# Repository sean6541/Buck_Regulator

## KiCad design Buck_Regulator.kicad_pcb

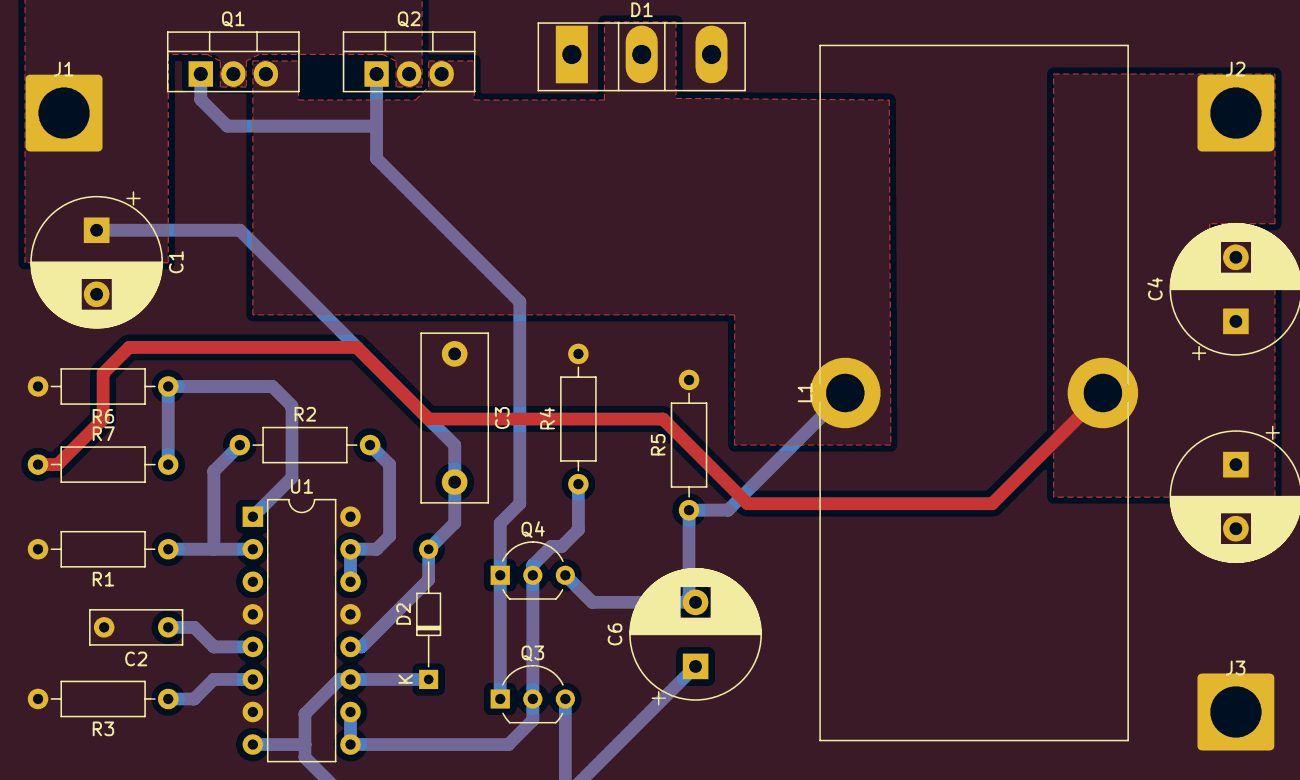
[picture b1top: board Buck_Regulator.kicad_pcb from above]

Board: 2 copper layers, 24 parts (0 on the bottom side), 12 nets.

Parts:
C1, C4, C5: 2200u; CP_Radial_D10.0mm_P5.00mm
C2: 1n; C_Disc_D7.0mm_W2.5mm_P5.00mm
C3: 0.1u; C_Rect_L13.0mm_W5.0mm_P10.00mm_FKS3_FKP3_MKS4
C6: 1u; CP_Radial_D10.0mm_P5.00mm
D1: D_Schottky_x2_KCom_AKA; TO-247-3_Vertical
D2: D; D_DO-34_SOD68_P10.16mm_Horizontal
J1, J2, J3: Screw_Terminal_01x01; SolderWire-2.5sqmm_1x01_D2.4mm_OD4.4mm
L1: 50u; L_Toroid_Vertical_L54.0mm_W23.8mm_P20.10mm_Bourns_5700
Q1, Q2: Q_NMOS_GDS; TO-220-3_Vertical
Q3: Q_NPN_EBC; TO-92_Inline_Wide
Q4: Q_PNP_EBC; TO-92_Inline_Wide
R1, R2: 5.1k; R_Axial_DIN0207_L6.3mm_D2.5mm_P10.16mm_Horizontal
R3: 7.5k; R_Axial_DIN0207_L6.3mm_D2.5mm_P10.16mm_Horizontal
R4: 10k; R_Axial_DIN0207_L6.3mm_D2.5mm_P10.16mm_Horizontal
R5: 470; R_Axial_DIN0207_L6.3mm_D2.5mm_P10.16mm_Horizontal
R6: 2k; R_Axial_DIN0207_L6.3mm_D2.5mm_P10.16mm_Horizontal
R7: 8.2k; R_Axial_DIN0207_L6.3mm_D2.5mm_P10.16mm_Horizontal
U1: TL494; DIP-16_W7.62mm

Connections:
+BATT: C1.1, C3.2, D2.2, J1.1, Q1.2, Q2.2, U1.12
GND: C1.2, C2.2, C3.1, C4.2, C5.2, D1.1, D1.3, J3.1, R1.2, R3.2, R4.2, R5.2, R6.2, U1.4, U1.7, U1.13, U1.16
unnamed: C2.1, U1.5
unnamed: C6.1, D2.1, Q3.3, U1.8, U1.11
unnamed: C6.2, D1.2, L1.1, Q1.3, Q2.3, Q4.3, R5.1
unnamed: Q1.1, Q2.1, Q3.1, Q4.1
unnamed: Q3.2, Q4.2, R4.1, U1.9, U1.10
unnamed: R1.1, R2.1, U1.2
unnamed: R2.2, U1.14, U1.15
unnamed: R3.1, U1.6
unnamed: R6.1, R7.2, U1.1
VCC: C4.1, C5.1, J2.1, L1.2, R7.1

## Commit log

2020-08-24 Initial
